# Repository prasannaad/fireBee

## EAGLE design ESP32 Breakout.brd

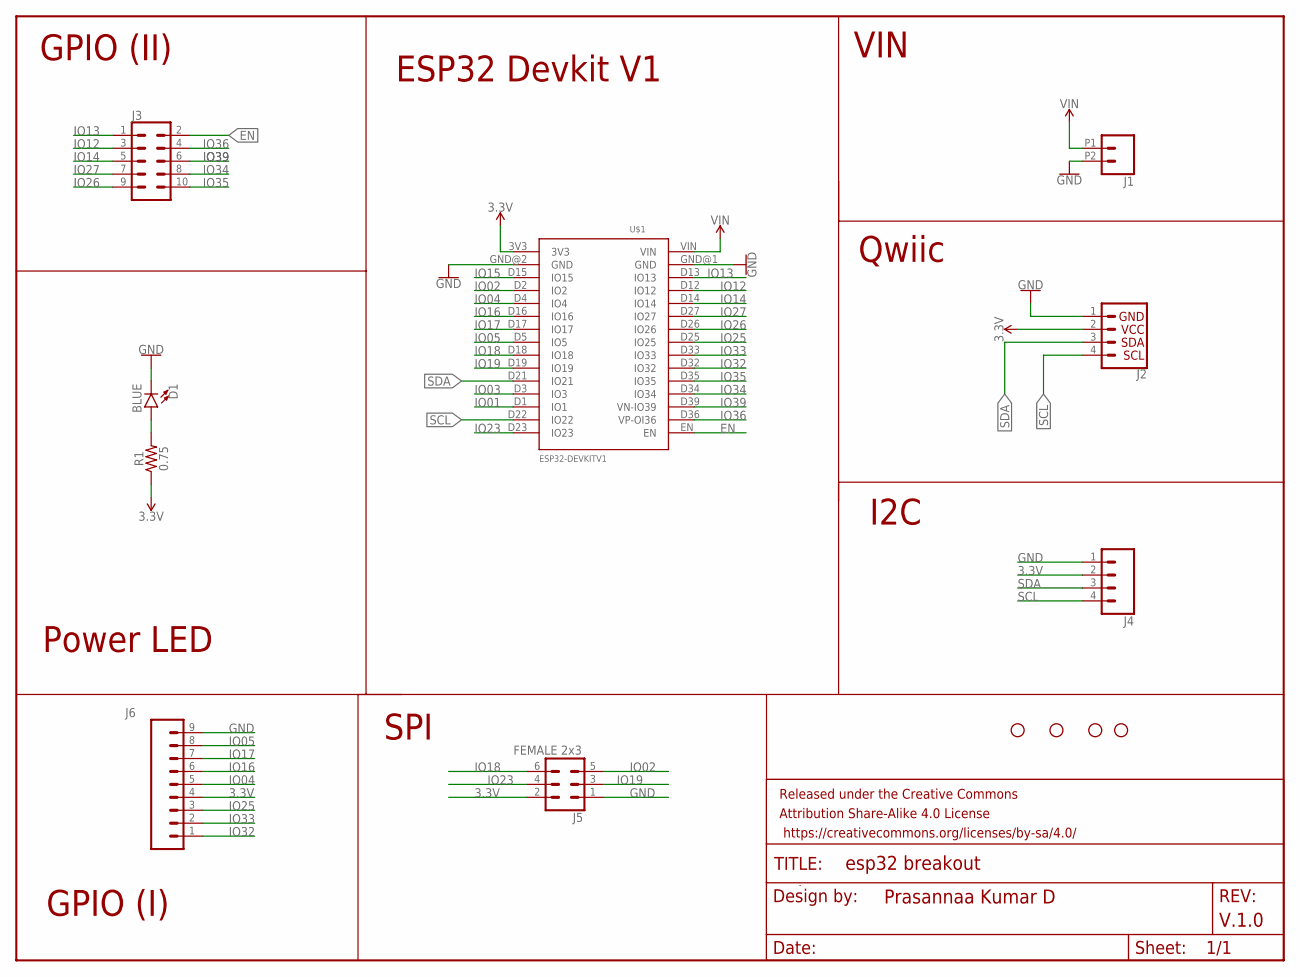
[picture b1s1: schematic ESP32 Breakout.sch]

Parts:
D1: BLUE; LED-1206
FRAME1: FRAME-LETTER; CREATIVE_COMMONS
H1, H2, H3, H4: STAND-OFFTIGHT; STAND-OFF-TIGHT
J1: CONN_022.54MM_SCREWTERM; 1X02_2.54_SCREWTERM
J2: QWIIC_CONNECTORJS-1MM; 1X04_1MM_RA
J3: CONN_05X2SHD; 2X5-SHROUDED
J4: CONN_041X04_NO_SILK; 1X04_NO_SILK
J5: FEMALE 2x3; 2X3
J6: CONN_09NO_SILK; 1X09_NO_SILK
R1: 0.75; 0805
U$1: ESP32DEVKITV1; ESP32-DEVKITV1

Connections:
3.3V: J2.2 (VCC), J4.2, J5.2, J6.4, R1.1, U$1.3V3
EN: J3.2, U$1.EN
GND: D1.C, J1.P2 (2), J2.1 (GND), J4.1, J5.1, J6.9, U$1.GND@1 (GND), U$1.GND@2 (GND)
IO01: U$1.D1 (IO1)
IO02: J5.5, U$1.D2 (IO2)
IO03: U$1.D3 (IO3)
IO04: J6.5, U$1.D4 (IO4)
IO05: J6.8, U$1.D5 (IO5)
IO12: J3.3, U$1.D12 (IO12)
IO13: J3.1, U$1.D13 (IO13)
IO14: J3.5, U$1.D14 (IO14)
IO15: U$1.D15 (IO15)
IO16: J6.6, U$1.D16 (IO16)
IO17: J6.7, U$1.D17 (IO17)
IO18: J5.6, U$1.D18 (IO18)
IO19: J5.3, U$1.D19 (IO19)
IO23: J5.4, U$1.D23 (IO23)
IO25: J6.3, U$1.D25 (IO25)
IO26: J3.9, U$1.D26 (IO26)
IO27: J3.7, U$1.D27 (IO27)
IO32: J6.1, U$1.D32 (IO32)
IO33: J6.2, U$1.D33 (IO33)
IO34: J3.8, U$1.D34 (IO34)
IO35: J3.10, U$1.D35 (IO35)
IO36: J3.4, U$1.D36 (VP-OI36)
IO39: J3.6, U$1.D39 (VN-IO39)
unnamed: D1.A, R1.2
SCL: J2.4 (SCL), J4.4, U$1.D22 (IO22)
SDA: J2.3 (SDA), J4.3, U$1.D21 (IO21)
VIN: J1.P1 (1), U$1.VIN

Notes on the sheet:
I2C
Qwiic
VIN
ESP32 Devkit V1
GPIO (II)
Power LED
GPIO (I)
SPI

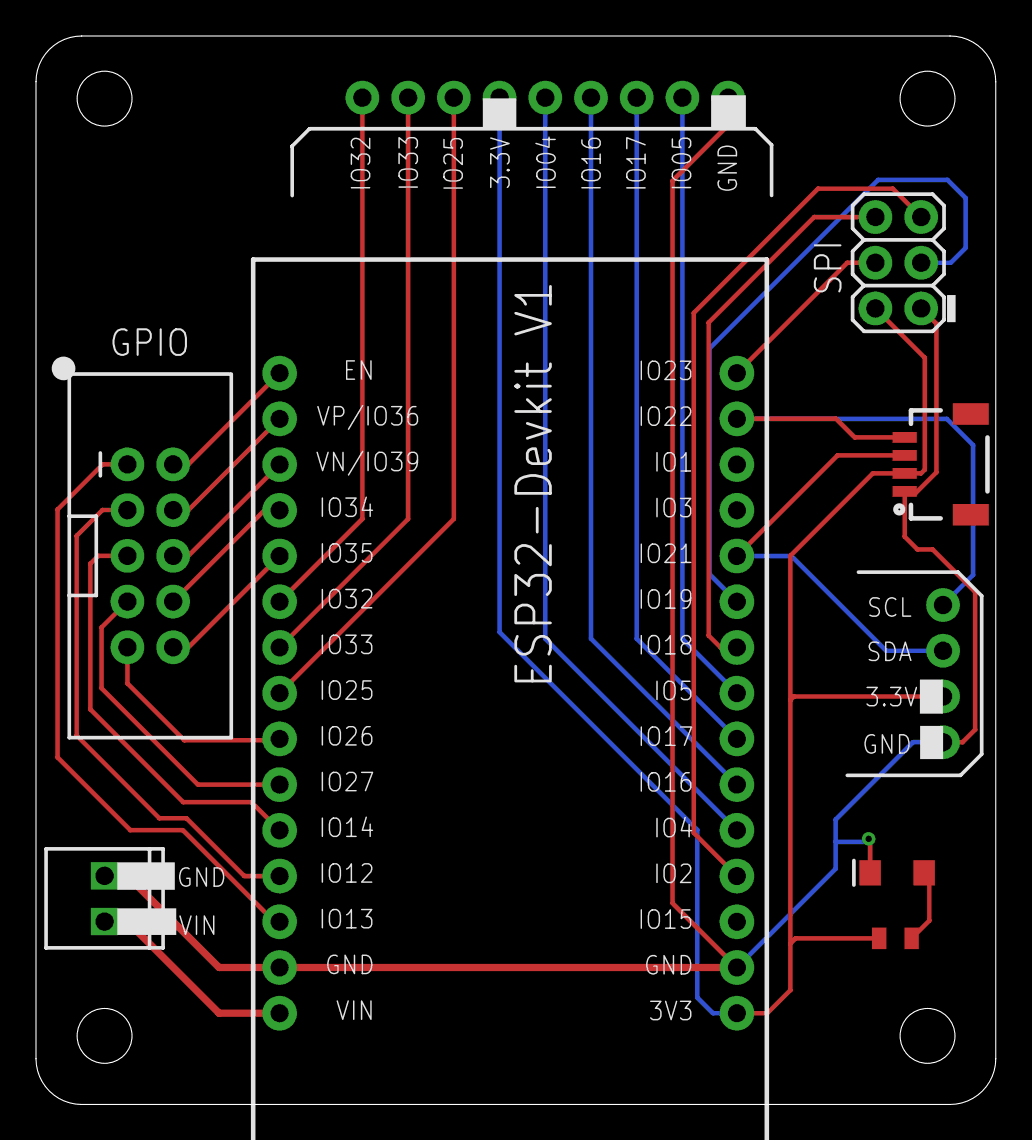
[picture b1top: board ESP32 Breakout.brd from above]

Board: 2 copper layers, 53.3 x 59.4 mm, 14 parts (0 on the bottom side), 27 nets.

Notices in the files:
parts and their libraries:
SparkFun-Connectors: Licensing: Creative Commons ShareAlike 4.0 International - https://creativecommons.org/licenses/by-sa/4.0
SparkFun-Aesthetics: Released under the Creative Commons Attribution Share-Alike 4.0 License
SparkFun-Aesthetics: https://creativecommons.org/licenses/by-sa/4.0
